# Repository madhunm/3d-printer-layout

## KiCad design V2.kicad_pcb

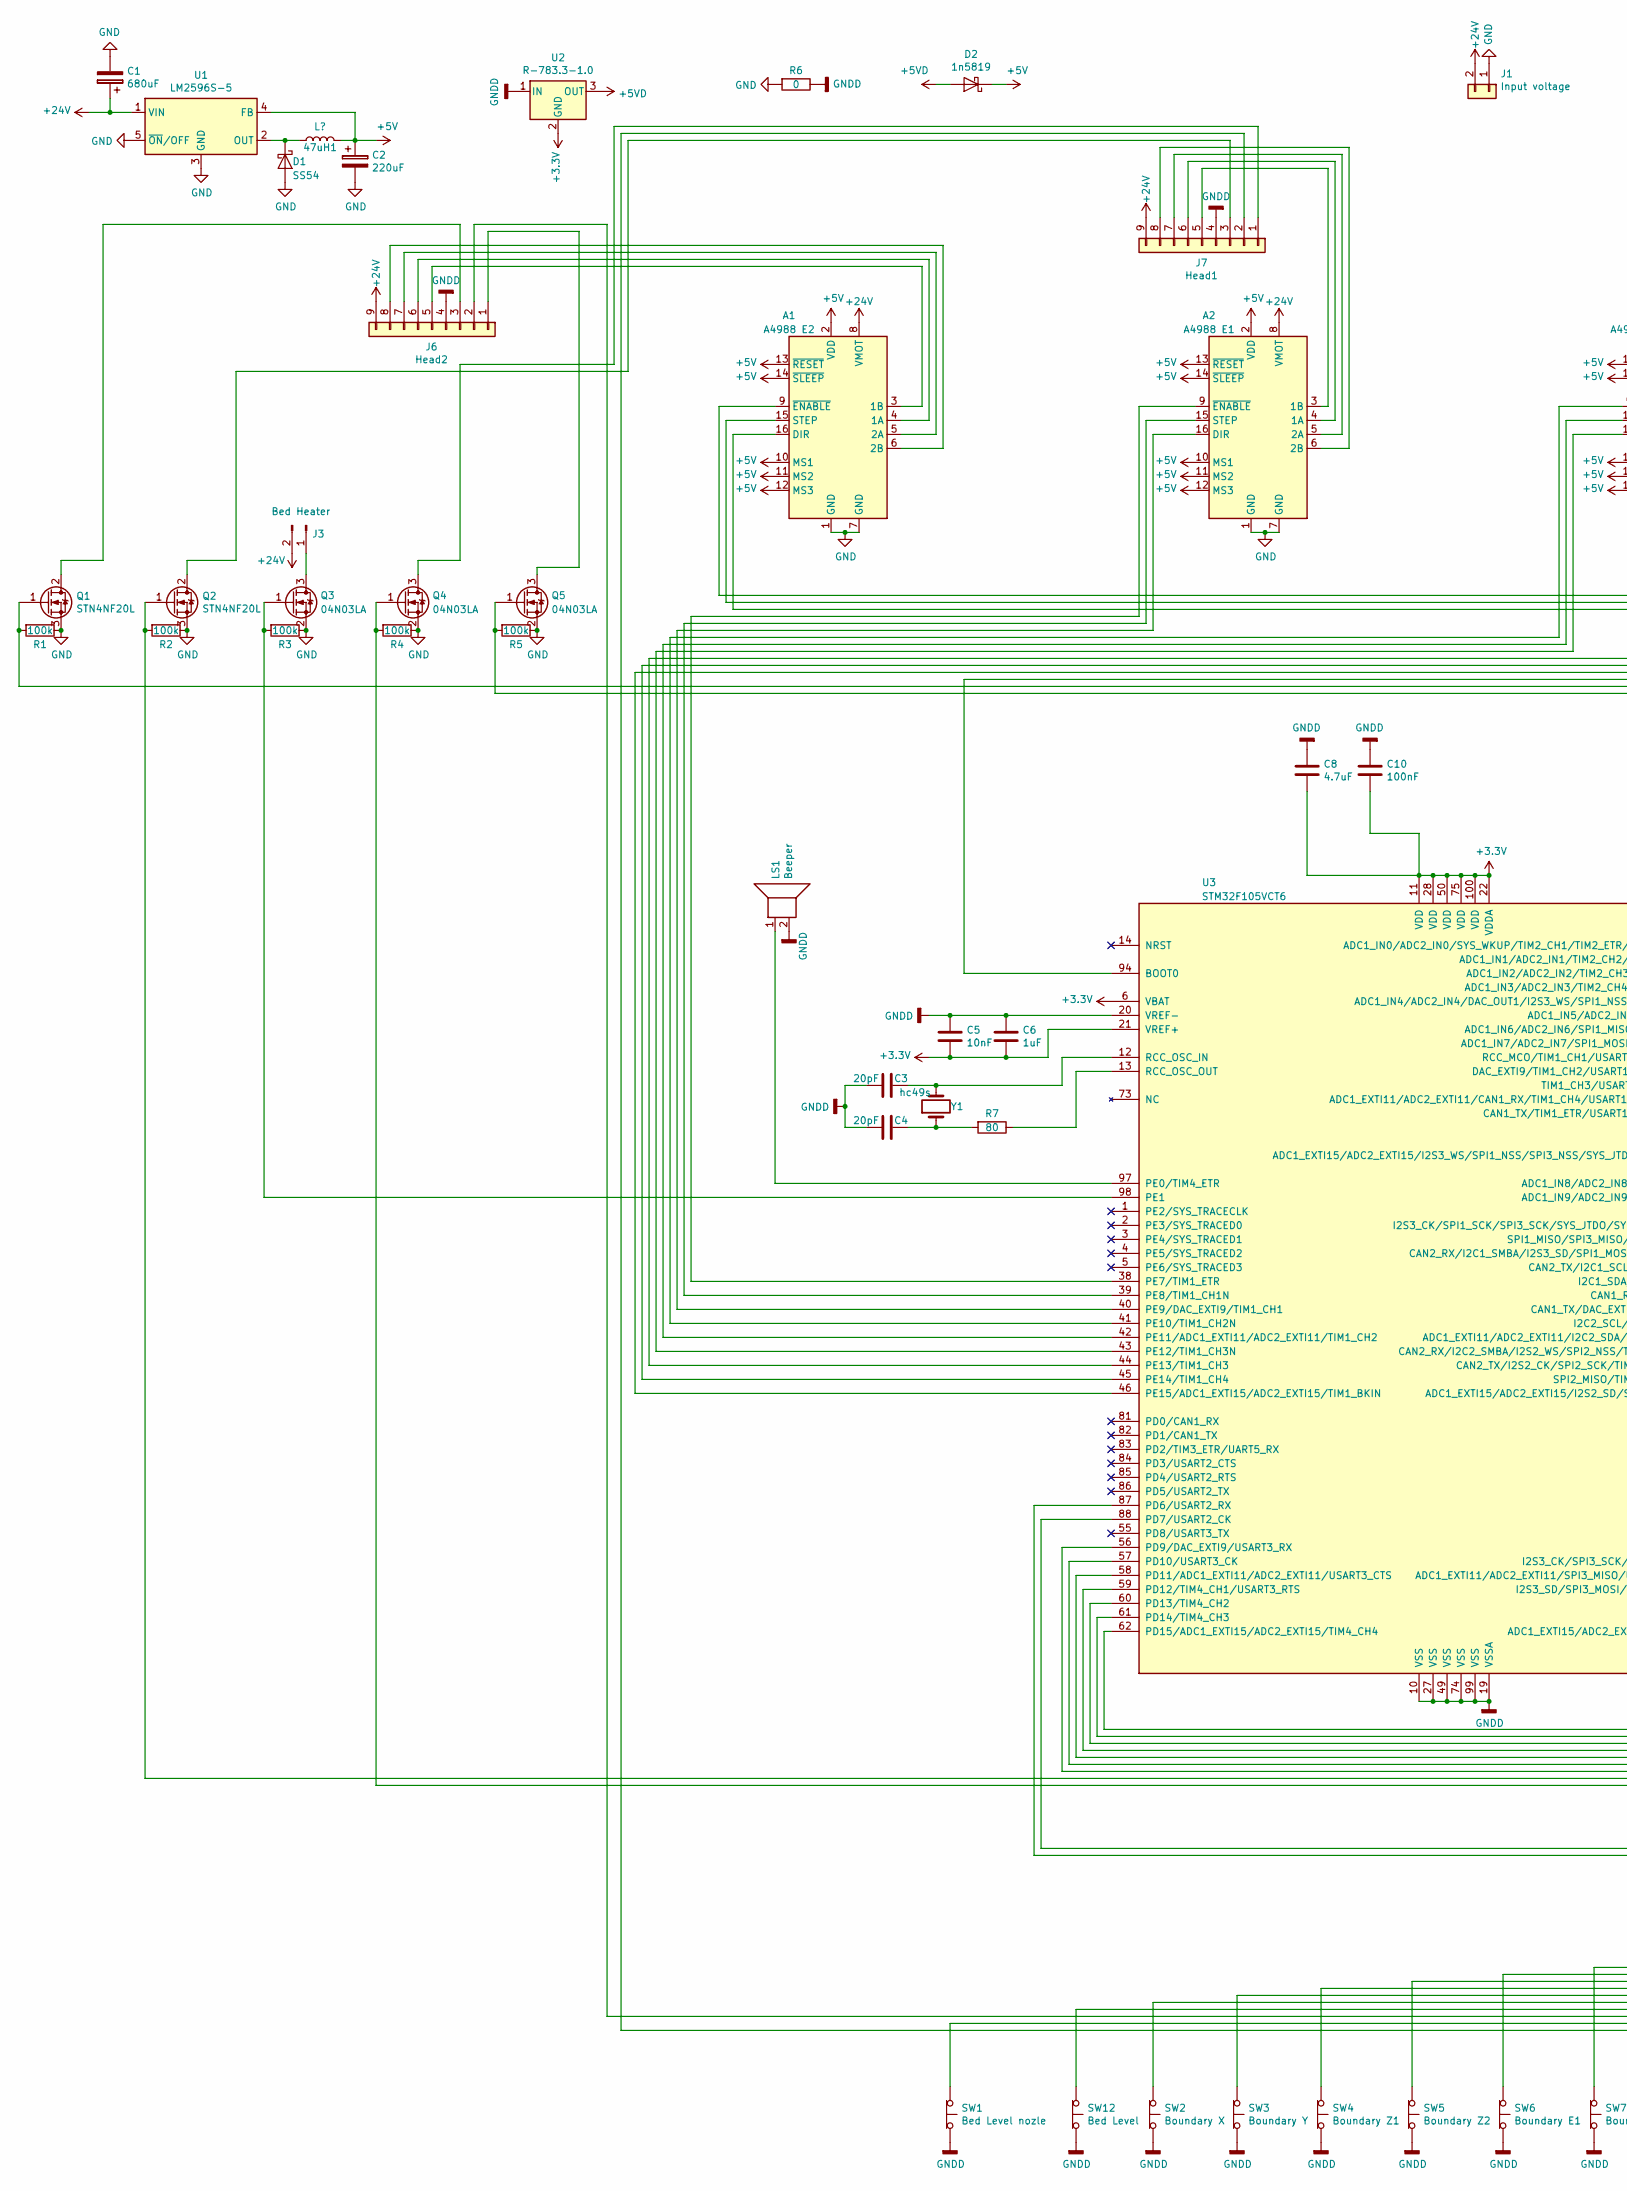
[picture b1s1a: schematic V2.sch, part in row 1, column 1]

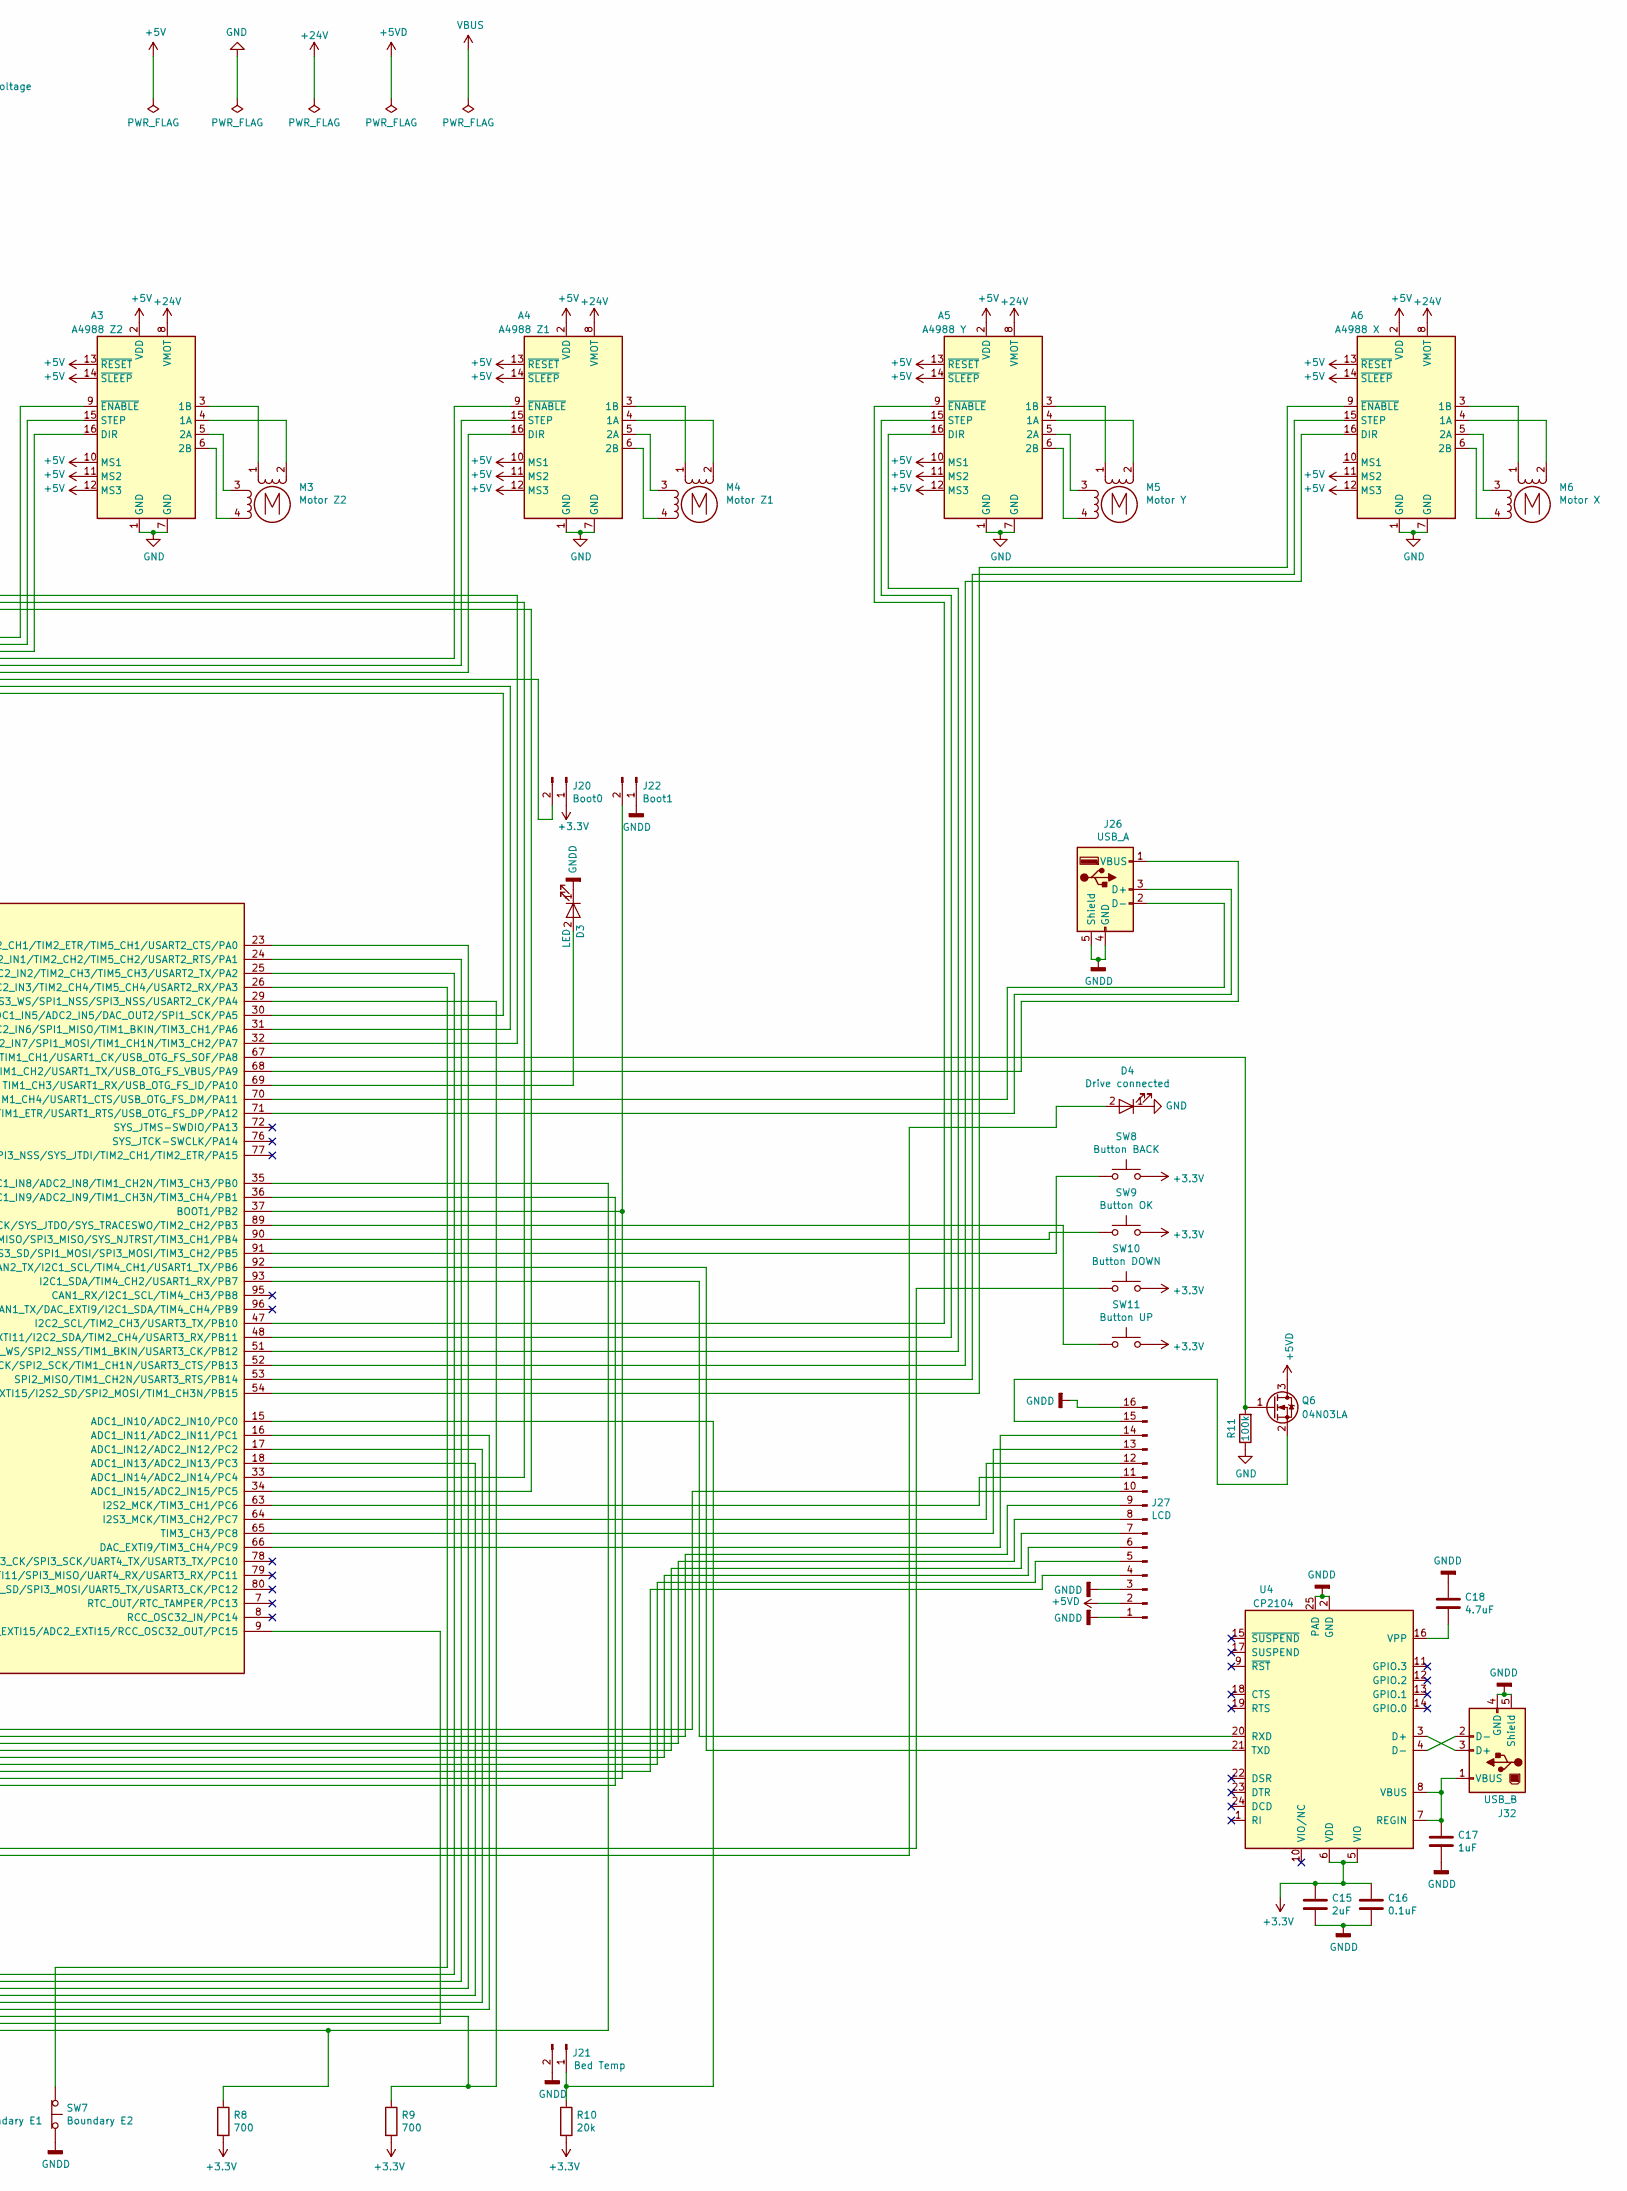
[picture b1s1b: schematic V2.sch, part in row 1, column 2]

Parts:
47uH1: L?; L_Radial_D12.0mm_P6.00mm_MuRATA_1900R
A1: A4988 E2; Pololu_Breakout-16_15.2x20.3mm
A2: A4988 E1; Pololu_Breakout-16_15.2x20.3mm
A3: A4988 Z2; Pololu_Breakout-16_15.2x20.3mm
A4: A4988 Z1; Pololu_Breakout-16_15.2x20.3mm
A5: A4988 Y; Pololu_Breakout-16_15.2x20.3mm
A6: A4988 X; Pololu_Breakout-16_15.2x20.3mm
C1: 680uF; CP_Radial_D10.0mm_P5.00mm
C2: 220uF; CP_Radial_D10.0mm_P7.50mm
C3, C4: 20pF; C_1206_3216Metric
C5: 10nF; C_1206_3216Metric
C6, C17: 1uF; C_1206_3216Metric
C8, C18: 4.7uF; C_1206_3216Metric
C10: 100nF; C_1206_3216Metric
C15: 2uF; C_1206_3216Metric
C16: 0.1uF; C_1206_3216Metric
D1: SS54; SS14
D2: 1n5819; do214ab
D3: LED; LED_D1.8mm_W1.8mm_H2.4mm_Horizontal_O1.27mm_Z1.6mm
D4: Drive connected; LED_D1.8mm_W1.8mm_H2.4mm_Horizontal_O1.27mm_Z1.6mm
J1: Input voltage; TerminalBlock_RND_205-00045_1x02_P5.00mm_Horizontal
J3: Bed Heater; TerminalBlock_RND_205-00045_1x02_P5.00mm_Horizontal
J6: Head2; JST_EH_B09B-EH-A_1x09_P2.50mm_Vertical
J7: Head1; JST_EH_B09B-EH-A_1x09_P2.50mm_Vertical
J20: Boot0; PinHeader_1x02_P2.54mm_Vertical
J21: Bed Temp; JST_EH_B02B-EH-A_1x02_P2.50mm_Vertical
J22: Boot1; PinHeader_1x02_P2.54mm_Vertical
J26: USB_A; conn_usb_A-vert2
J27: LCD; lcd_20x4
J32: USB_B; USB_B_OST_USB-B1HSxx_Horizontal
LS1: Beeper; Buzzer_12x9.5RM7.6
M3: Motor Z2; JST_EH_B04B-EH-A_1x04_P2.50mm_Vertical
M4: Motor Z1; JST_EH_B04B-EH-A_1x04_P2.50mm_Vertical
M5: Motor Y; JST_EH_B04B-EH-A_1x04_P2.50mm_Vertical
M6: Motor X; JST_EH_B04B-EH-A_1x04_P2.50mm_Vertical
Q1, Q2: STN4NF20L; TO-252-2
Q3, Q4, Q5, Q6: 04N03LA; TO-252-2
R1, R2, R3, R4, R5, R11: 100k; R_1206_3216Metric
R6: 0; R_0603_1608Metric
R7: 80; R_1206_3216Metric
R8, R9: 700; R_1206_3216Metric
R10: 20k; R_1206_3216Metric
SW1: Bed Level nozle; JST_EH_B02B-EH-A_1x02_P2.50mm_Vertical
SW2: Boundary X; JST_EH_B02B-EH-A_1x02_P2.50mm_Vertical
SW3: Boundary Y; JST_EH_B02B-EH-A_1x02_P2.50mm_Vertical
SW4: Boundary Z1; JST_EH_B02B-EH-A_1x02_P2.50mm_Vertical
SW5: Boundary Z2; JST_EH_B02B-EH-A_1x02_P2.50mm_Vertical
SW6: Boundary E1; JST_EH_B02B-EH-A_1x02_P2.50mm_Vertical
SW7: Boundary E2; JST_EH_B02B-EH-A_1x02_P2.50mm_Vertical
SW8: Button BACK; SW_PUSH_6mm
SW9: Button OK; SW_PUSH_6mm
SW10: Button DOWN; SW_PUSH_6mm
SW11: Button UP; SW_PUSH_6mm
SW12: Bed Level; JST_EH_B02B-EH-A_1x02_P2.50mm_Vertical
U1: LM2596S-5; TO-263-5_TabPin3
U2: R-783.3-1.0; SOT-223-3_TabPin2
U3: STM32F105VCT6; LQFP-100_14x14mm_P0.5mm
U4: CP2104; QFN-24-1EP_4x4mm_P0.5mm_EP2.7x2.7mm
Y1: hc49s; Crystal_HC49-4H_Vertical

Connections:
+3V3: C5.2, C6.2, C8.2, C10.2, C15.1, C16.1, J20.1, R8.2, R9.2, R10.2, SW8.2, SW9.2, SW10.2, SW11.2, U2.2 (GND), U3.6 (VBAT), U3.11 (VDD), U3.21 (VREF+), U3.22 (VDDA), U3.28 (VDD), U3.50 (VDD), U3.75 (VDD), U3.100 (VDD), U4.5 (VIO), U4.6 (VDD)
+5V: 47uH1.2, A1.2 (VDD), A1.10 (MS1), A1.11 (MS2), A1.12 (MS3), A1.13 (~RESET), A1.14 (~SLEEP), A2.2 (VDD), A2.10 (MS1), A2.11 (MS2), A2.12 (MS3), A2.13 (~RESET), A2.14 (~SLEEP), A3.2 (VDD), A3.10 (MS1), A3.11 (MS2), A3.12 (MS3), A3.13 (~RESET), A3.14 (~SLEEP), A4.2 (VDD), A4.10 (MS1), A4.11 (MS2), A4.12 (MS3), A4.13 (~RESET), A4.14 (~SLEEP), A5.2 (VDD), A5.10 (MS1), A5.11 (MS2), A5.12 (MS3), A5.13 (~RESET), A5.14 (~SLEEP), A6.2 (VDD), A6.11 (MS2), A6.12 (MS3), A6.13 (~RESET), A6.14 (~SLEEP), C2.1, D2.1 (K), U1.4 (FB)
+5VD: D2.2 (A), J27.2, Q6.3 (D), U2.3 (OUT)
+24V: A1.8 (VMOT), A2.8 (VMOT), A3.8 (VMOT), A4.8 (VMOT), A5.8 (VMOT), A6.8 (VMOT), C1.1, J1.2, J3.2, J6.9, J7.9, U1.1 (VIN)
GND: A1.1 (GND), A1.7 (GND), A2.1 (GND), A2.7 (GND), A3.1 (GND), A3.7 (GND), A4.1 (GND), A4.7 (GND), A5.1 (GND), A5.7 (GND), A6.1 (GND), A6.7 (GND), C1.2, C2.2, D1.2 (A), D4.1 (K), J1.1, Q1.3 (S), Q2.3 (S), Q3.2 (S), Q4.2 (S), Q5.2 (S), R1.1, R2.1, R3.1, R4.1, R5.1, R6.2, R11.1, U1.3 (GND), U1.5 (~ON~/OFF)
GNDD: C3.2, C4.2, C5.1, C6.1, C8.1, C10.1, C15.2, C16.2, C17.2, C18.1, D3.1 (K), J6.4, J7.4, J21.2, J22.1, J26.4 (GND), J26.5 (Shield), J27.1, J27.3, J27.16, J32.4 (GND), J32.5 (Shield), LS1.2, R6.1, SW1.2 (B), SW2.2 (B), SW3.2 (B), SW4.2 (B), SW5.2 (B), SW6.2 (B), SW7.2 (B), SW12.2 (B), U2.1 (IN), U3.10 (VSS), U3.19 (VSSA), U3.20 (VREF-), U3.27 (VSS), U3.49 (VSS), U3.74 (VSS), U3.99 (VSS), U4.2 (GND), U4.25 (PAD)
unnamed: 47uH1.1, D1.1 (K), U1.2 (OUT)
unnamed: A1.3 (1B), J6.5
unnamed: A1.4 (1A), J6.6
unnamed: A1.5 (2A), J6.7
unnamed: A1.6 (2B), J6.8
unnamed: A1.9 (~ENABLE), U3.32 (ADC1_IN7/ADC2_IN7/SPI1_MOSI/TIM1_CH1N/T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)
unnamed: A1.15 (STEP), U3.33 (ADC1_IN14/ADC2_IN14/PC4)
unnamed: A1.16 (DIR), U3.34 (ADC1_IN15/ADC2_IN15/PC5)
unnamed: A2.3 (1B), J7.5
unnamed: A2.4 (1A), J7.6
unnamed: A2.5 (2A), J7.7
unnamed: A2.6 (2B), J7.8
unnamed: A2.9 (~ENABLE), U3.38 (PE7/TIM1_ETR)
unnamed: A2.15 (STEP), U3.39 (PE8/TIM1_CH1N)
unnamed: A2.16 (DIR), U3.40 (PE9/DAC_EXTI9/TIM1_CH1)
unnamed: A3.3 (1B), M3.1
unnamed: A3.4 (1A), M3.2 (-)
unnamed: A3.5 (2A), M3.3
unnamed: A3.6 (2B), M3.4
unnamed: A3.9 (~ENABLE), U3.41 (PE10/TIM1_CH2N)
unnamed: A3.15 (STEP), U3.42 (PE11/ADC1_EXTI11/ADC2_EXTI11/TIM1_CH2)
unnamed: A3.16 (DIR), U3.43 (PE12/TIM1_CH3N)
unnamed: A4.3 (1B), M4.1
unnamed: A4.4 (1A), M4.2 (-)
unnamed: A4.5 (2A), M4.3
unnamed: A4.6 (2B), M4.4
unnamed: A4.9 (~ENABLE), U3.44 (PE13/TIM1_CH3)
unnamed: A4.15 (STEP), U3.45 (PE14/TIM1_CH4)
unnamed: A4.16 (DIR), U3.46 (PE15/ADC1_EXTI15/ADC2_EXTI15/TIM1_BKIN)
unnamed: A5.3 (1B), M5.1
unnamed: A5.4 (1A), M5.2 (-)
unnamed: A5.5 (2A), M5.3
unnamed: A5.6 (2B), M5.4
unnamed: A5.9 (~ENABLE), U3.47 (I2C2_SCL/TIM2_CH3/USART3_TX/PB10)
unnamed: A5.15 (STEP), U3.48 (ADC1_EXTI11/ADC2_EXTI11/I2C2_SDA/TIM2_C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)
unnamed: A5.16 (DIR), U3.51 (CAN2_RX/I2C2_SMBA/I2S2_WS/SPI2_NSS/TIM1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)
unnamed: A6.3 (1B), M6.1
unnamed: A6.4 (1A), M6.2 (-)
unnamed: A6.5 (2A), M6.3
unnamed: A6.6 (2B), M6.4
unnamed: A6.9 (~ENABLE), U3.54 (ADC1_EXTI15/ADC2_EXTI15/I2S2_SD/SPI2_MO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)
unnamed: A6.15 (STEP), U3.53 (SPI2_MISO/TIM1_CH2N/USART3_RTS/PB14)
unnamed: A6.16 (DIR), U3.52 (CAN2_TX/I2S2_CK/SPI2_SCK/TIM1_CH1N/USAR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)
unnamed: C3.1, U3.12 (RCC_OSC_IN), Y1.2
unnamed: C4.1, R7.2, Y1.1
unnamed: C17.1, J32.1 (VBUS), U4.7 (REGIN), U4.8 (VBUS)
unnamed: C18.2, U4.16 (VPP)
unnamed: D3.2 (A), U3.69 (TIM1_CH3/USART1_RX/USB_OTG_FS_ID/PA10)
unnamed: D4.2 (A), U3.87 (PD6/USART2_RX)
unnamed: J3.1, Q3.3 (D)
unnamed: J6.1, Q5.3 (D)
unnamed: J6.2, R9.1, U3.29 (ADC1_IN4/ADC2_IN4/DAC_OUT1/I2S3_WS/SPI1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)
unnamed: J6.3, Q1.2 (D)
unnamed: J7.1, Q4.3 (D)
unnamed: J7.2, R8.1, U3.35 (ADC1_IN8/ADC2_IN8/TIM1_CH2N/TIM3_CH3/PB0)
unnamed: J7.3, Q2.2 (D)
unnamed: J20.2, U3.94 (BOOT0)
unnamed: J21.1, R10.1, U3.15 (ADC1_IN10/ADC2_IN10/PC0)
unnamed: J22.2, Q2.1 (G), R2.2, U3.37 (BOOT1/PB2)
unnamed: J26.1 (VBUS), U3.68 (DAC_EXTI9/TIM1_CH2/USART1_TX/USB_OTG_FS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)
unnamed: J26.2 (D-), U3.70 (ADC1_EXTI11/ADC2_EXTI11/CAN1_RX/TIM1_CH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)
unnamed: J26.3 (D+), U3.71 (CAN1_TX/TIM1_ETR/USART1_RTS/USB_OTG_FS_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)
unnamed: J27.4, U3.56 (PD9/DAC_EXTI9/USART3_RX)
unnamed: J27.5, U3.57 (PD10/USART3_CK)
unnamed: J27.6, U3.58 (PD11/ADC1_EXTI11/ADC2_EXTI11/USART3_CTS)
unnamed: J27.7, U3.59 (PD12/TIM4_CH1/USART3_RTS)
unnamed: J27.8, U3.60 (PD13/TIM4_CH2)
unnamed: J27.9, U3.61 (PD14/TIM4_CH3)
unnamed: J27.10, U3.62 (PD15/ADC1_EXTI15/ADC2_EXTI15/TIM4_CH4)
unnamed: J27.11, U3.63 (I2S2_MCK/TIM3_CH1/PC6)
unnamed: J27.12, U3.64 (I2S3_MCK/TIM3_CH2/PC7)
unnamed: J27.13, U3.65 (TIM3_CH3/PC8)
unnamed: J27.14, U3.66 (DAC_EXTI9/TIM3_CH4/PC9)
unnamed: J27.15, Q6.2 (S)
unnamed: J32.2 (D-), U4.4 (D-)
unnamed: J32.3 (D+), U4.3 (D+)
unnamed: LS1.1, U3.97 (PE0/TIM4_ETR)
unnamed: Q1.1 (G), R1.2, U3.31 (ADC1_IN6/ADC2_IN6/SPI1_MISO/TIM1_BKIN/T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)
unnamed: Q3.1 (G), R3.2, U3.98 (PE1)
unnamed: Q4.1 (G), R4.2, U3.36 (ADC1_IN9/ADC2_IN9/TIM1_CH3N/TIM3_CH4/PB1)
unnamed: Q5.1 (G), R5.2, U3.30 (ADC1_IN5/ADC2_IN5/DAC_OUT2/SPI1_SCK/PA5)
unnamed: Q6.1 (G), R11.2, U3.67 (RCC_MCO/TIM1_CH1/USART1_CK/USB_OTG_FS_S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)
unnamed: R7.1, U3.13 (RCC_OSC_OUT)
unnamed: SW1.1 (A), U3.9 (ADC1_EXTI15/ADC2_EXTI15/RCC_OSC32_OUT/P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)
unnamed: SW2.1 (A), U3.17 (ADC1_IN12/ADC2_IN12/PC2)
unnamed: SW3.1 (A), U3.18 (ADC1_IN13/ADC2_IN13/PC3)
unnamed: SW4.1 (A), U3.23 (ADC1_IN0/ADC2_IN0/SYS_WKUP/TIM2_CH1/TIM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)
unnamed: SW5.1 (A), U3.24 (ADC1_IN1/ADC2_IN1/TIM2_CH2/TIM5_CH2/USA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)
unnamed: SW6.1 (A), U3.25 (ADC1_IN2/ADC2_IN2/TIM2_CH3/TIM5_CH3/USA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)
unnamed: SW7.1 (A), U3.26 (ADC1_IN3/ADC2_IN3/TIM2_CH4/TIM5_CH4/USA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)
unnamed: SW8.1, U3.91 (CAN2_RX/I2C1_SMBA/I2S3_SD/SPI1_MOSI/SPI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)
unnamed: SW9.1, U3.90 (SPI1_MISO/SPI3_MISO/SYS_NJTRST/TIM3_CH1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)
unnamed: SW10.1, U3.88 (PD7/USART2_CK)
unnamed: SW11.1, U3.89 (I2S3_CK/SPI1_SCK/SPI3_SCK/SYS_JTDO/SYS_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)
unnamed: SW12.1 (A), U3.16 (ADC1_IN11/ADC2_IN11/PC1)
unnamed: U3.92 (CAN2_TX/I2C1_SCL/TIM4_CH1/USART1_TX/PB6), U4.21 (TXD)
unnamed: U3.93 (I2C1_SDA/TIM4_CH2/USART1_RX/PB7), U4.20 (RXD)

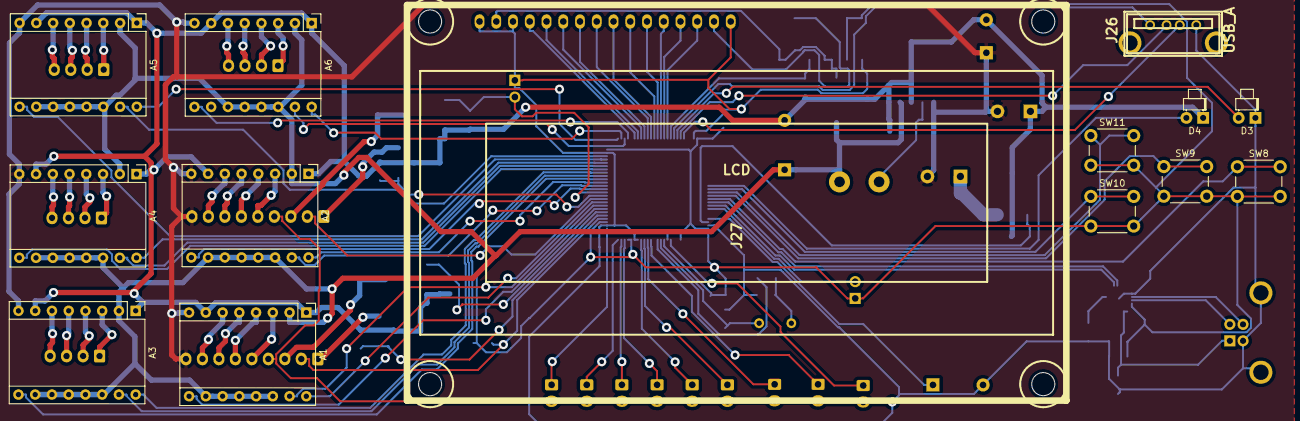
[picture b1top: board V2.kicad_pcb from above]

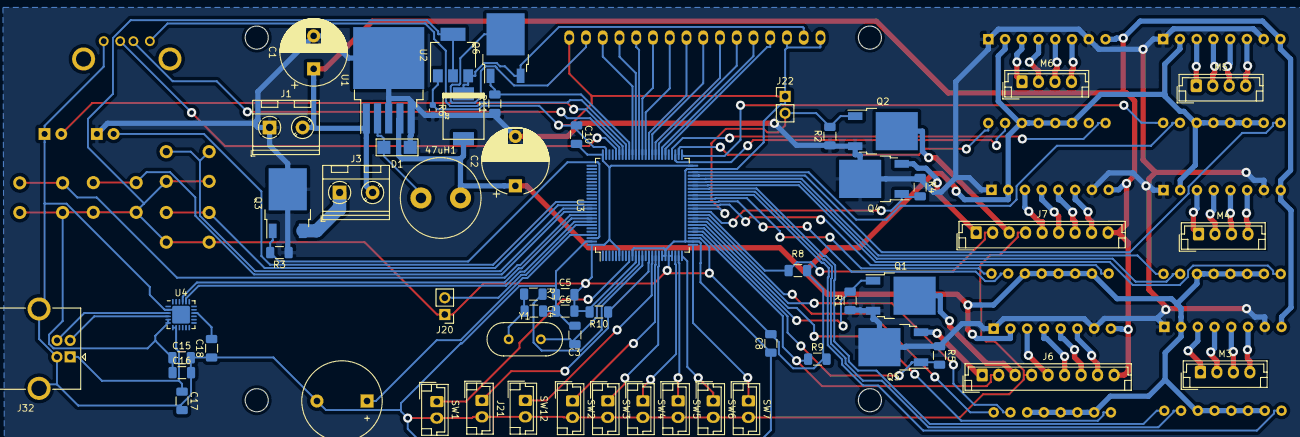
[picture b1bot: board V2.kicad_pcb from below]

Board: 2 copper layers, 72 parts (58 on the bottom side), 103 nets.

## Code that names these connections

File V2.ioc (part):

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Mcu.Name=STM32F105V(8-B-C)Tx
Mcu.Package=LQFP100
Mcu.UserName=STM32F105VCTx
PA10.GPIOParameters=GPIO_Label
PA10.GPIO_Label=DRIVE_FS???
PA10.Signal=GPIO_Output
PA11.Mode=Host_Only
PA11.Signal=USB_OTG_FS_DM
PA12.Mode=Host_Only
PA12.Signal=USB_OTG_FS_DP
PA14.GPIOParameters=GPIO_Label
PA14.GPIO_Label=DIR X
PA14.Signal=GPIO_Output
PA15.GPIOParameters=GPIO_Label
PA15.GPIO_Label=STEP X
PA15.Signal=GPIO_Output
PA2.GPIOParameters=GPIO_Label
PA2.GPIO_Label=Bed Temperature
PA2.Signal=ADCx_IN2
PA3.GPIOParameters=GPIO_PuPd,GPIO_Label
PA3.GPIO_Label=Bed Level Input
PA3.GPIO_PuPd=GPIO_PULLUP
PA3.Signal=GPIO_Input
PA4.GPIOParameters=GPIO_PuPd,GPIO_Label
PA4.GPIO_Label=Boundary X
PA4.GPIO_PuPd=GPIO_PULLUP
PA4.Signal=GPIO_Input
PA5.GPIOParameters=GPIO_PuPd,GPIO_Label
PA5.GPIO_Label=Boundary Y
PA5.GPIO_PuPd=GPIO_PULLUP
PA5.Signal=GPIO_Input
PA6.GPIOParameters=GPIO_PuPd,GPIO_Label
PA6.GPIO_Label=Boundary Z1
PA6.GPIO_PuPd=GPIO_PULLUP
PA6.Signal=GPIO_Input
PA7.GPIOParameters=GPIO_PuPd,GPIO_Label
PA7.GPIO_Label=Boundary Z2
PA7.GPIO_PuPd=GPIO_PULLUP
PA7.Signal=GPIO_Input
PA8.GPIOParameters=GPIO_Label
PA8.GPIO_Label=USB Ready LED
PA8.Signal=GPIO_Output
PA9.Mode=Activate_VBUS
PA9.Signal=USB_OTG_FS_VBUS
PB0.GPIOParameters=GPIO_Label
PB0.GPIO_Label=Extr1 Temperature
PB0.Signal=ADCx_IN8
PB1.GPIOParameters=GPIO_Label
PB1.GPIO_Label=Extr2 Temperature
PB1.Signal=ADCx_IN9
PB12.GPIOParameters=GPIO_Label
PB12.GPIO_Label=LCD RS
PB12.Signal=GPIO_Output
PB13.GPIOParameters=GPIO_Label
PB13.GPIO_Label=LCD RW
PB13.Signal=GPIO_Output
PB14.GPIOParameters=GPIO_Label
PB14.GPIO_Label=LCD EN
PB14.Signal=GPIO_Output
PB15.GPIOParameters=GPIO_Label
PB15.GPIO_Label=LCD DB0
PB15.Signal=GPIO_Output
PB3.GPIOParameters=GPIO_Label
PB3.GPIO_Label=STEP E1
PB3.Signal=GPIO_Output
PB4.GPIOParameters=GPIO_Label
PB4.GPIO_Label=EN E1
PB4.Signal=GPIO_Output
PB5.GPIOParameters=GPIO_Label
PB5.GPIO_Label=DIR E2
PB5.Signal=GPIO_Output
PB8.GPIOParameters=GPIO_Label
PB8.GPIO_Label=Extr1 Heater
PB8.Signal=GPIO_Output
PB9.GPIOParameters=GPIO_Label
PB9.GPIO_Label=Bed Heater
PB9.Signal=GPIO_Output
PC10.GPIOParameters=GPIO_Label
PC10.GPIO_Label=EN X
PC10.Signal=GPIO_Output
PC11.GPIOParameters=GPIO_Label
PC11.GPIO_Label=DIR Y
PC11.Signal=GPIO_Output
PC12.GPIOParameters=GPIO_Label
PC12.GPIO_Label=STEP Y
PC12.Signal=GPIO_Output
PC13-TAMPER-RTC.GPIOParameters=GPIO_Label
PC13-TAMPER-RTC.GPIO_Label=EN E2
PC13-TAMPER-RTC.Signal=GPIO_Output
PC14-OSC32_IN.GPIOParameters=GPIO_Label
PC14-OSC32_IN.GPIO_Label=STEP E2
PC14-OSC32_IN.Signal=GPIO_Output
PC4.GPIOParameters=GPIO_PuPd,GPIO_Label
PC4.GPIO_Label=Boundary E1
PC4.GPIO_PuPd=GPIO_PULLUP
PC4.Signal=GPIO_Input
PC5.GPIOParameters=GPIO_PuPd,GPIO_Label
PC5.GPIO_Label=Boundary E2
PC5.GPIO_PuPd=GPIO_PULLUP
PC5.Signal=GPIO_Input
PC6.GPIOParameters=GPIO_PuPd,GPIO_Label
PC6.GPIO_Label=Button UP
PC6.GPIO_PuPd=GPIO_PULLDOWN
PC6.Signal=GPIO_Input
PC7.GPIOParameters=GPIO_PuPd,GPIO_Label
PC7.GPIO_Label=Button DOWN
PC7.GPIO_PuPd=GPIO_PULLDOWN
PC7.Signal=GPIO_Input
PC8.GPIOParameters=GPIO_PuPd,GPIO_Label
PC8.GPIO_Label=Button OK
PC8.GPIO_PuPd=GPIO_PULLDOWN
PC8.Signal=GPIO_Input
PC9.GPIOParameters=GPIO_PuPd,GPIO_Label
PC9.GPIO_Label=Button BACK
PC9.GPIO_PuPd=GPIO_PULLDOWN
PC9.Signal=GPIO_Input
PD0.GPIOParameters=GPIO_Label
PD0.GPIO_Label=EN Y
PD0.Signal=GPIO_Output
PD1.GPIOParameters=GPIO_Label
PD1.GPIO_Label=DIR Z1
PD1.Signal=GPIO_Output
PD10.GPIOParameters=GPIO_Label
PD10.GPIO_Label=LCD DB3
PD10.Signal=GPIO_Output
PD11.GPIOParameters=GPIO_Label
PD11.GPIO_Label=LCD DB4
PD11.Signal=GPIO_Output
PD12.GPIOParameters=GPIO_Label
PD12.GPIO_Label=LCD DB5
PD12.Signal=GPIO_Output
PD13.GPIOParameters=GPIO_Label
PD13.GPIO_Label=LCD DB6
PD13.Signal=GPIO_Output
PD14.GPIOParameters=GPIO_Label
PD14.GPIO_Label=LCD DB7
PD14.Signal=GPIO_Output
PD15.GPIOParameters=GPIO_Label
PD15.GPIO_Label=Beeper
PD15.Signal=GPIO_Output
PD2.GPIOParameters=GPIO_Label
PD2.GPIO_Label=STEP Z1
PD2.Signal=GPIO_Output
PD3.GPIOParameters=GPIO_Label
PD3.GPIO_Label=EN Z1
PD3.Signal=GPIO_Output
PD4.GPIOParameters=GPIO_Label
PD4.GPIO_Label=DIR Z2
PD4.Signal=GPIO_Output
PD5.GPIOParameters=GPIO_Label
PD5.GPIO_Label=STEP Z2
PD5.Signal=GPIO_Output
PD6.GPIOParameters=GPIO_Label
PD6.GPIO_Label=EN Z2
PD6.Signal=GPIO_Output
PD7.GPIOParameters=GPIO_Label
PD7.GPIO_Label=DIR E1
PD7.Signal=GPIO_Output
PD8.GPIOParameters=GPIO_Label
PD8.GPIO_Label=LCD DB1
PD8.Signal=GPIO_Output
PD9.GPIOParameters=GPIO_Label
PD9.GPIO_Label=LCD DB2
PD9.Signal=GPIO_Output
PE0.GPIOParameters=GPIO_Label
PE0.GPIO_Label=Extr Cooler 1
PE0.Signal=GPIO_Output
PE1.GPIOParameters=GPIO_Label
PE1.GPIO_Label=Extr Cooler 2
PE1.Signal=GPIO_Output
PE2.GPIOParameters=GPIO_Label
PE2.GPIO_Label=Extr2 Heater
PE2.Signal=GPIO_Output
RCC.SYSCLKFreq_VALUE=72000000
RCC.SYSCLKSource=RCC_SYSCLKSOURCE_PLLCLK
board=custom

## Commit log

2019-01-24 this is layout
2019-01-24 this is layout and file STM32CubeMX
2019-01-27 Fix ERC
2019-01-30 footprints are added
2019-02-09 netlist with pcb
2019-02-26 много изменений, поэтому новый бранч
2019-03-15 Драйвера перенесены вбок, новая распиновка
2019-03-19 Vias clearence and vias diameter are increased
2019-06-01 Новая версия
2019-06-04 переразвёл заново
